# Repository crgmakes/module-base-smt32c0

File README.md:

# Servo Module

All the source files for the module template for SMT32C0-based module hardware.

# Software 

You will need [KiCad](https://kicad.org) to view and edit this design. Click [here](https://www.kicad.org/download/) to download.

You will also need all the associated libraries and models to drive the design if you want to make changes or view the 3D rendering:

https://github.com/crgmakes/kicad-library.git

Kicad MUST be configured properly to use all the files in this repo. Once you have Kicad installed, under Preferences->Configure Paths..., make the following entries:

1 - KICAD_USER_DIR -> set to the root location of where you placed the above repository.
2 - KICAD_USER_LIBRARY = ${KICAD_USER_DIR}/Library
3 - KICAD_USER_MODEL_DIR = ${KICAD_USER_LIBRARY}/models
4 - KICAD_USER_TEMPLATE_DIR	= ${KICAD_USER_LIBRARY}/templates	

Kicad will operate mostly normally if these are not set properly. You will notice an issue when you view the PCB in 3D mode.

***NOTE***: after makeing a release build in git, if your rendered 3D images are missing components, ensure the path to EVERY component model is set to ${KICAD_USER_MODEL_DIR}/<model name>.

Kicad sometimes replaces the variable with an expansion and that FAILS during the build process because the expanded variable is local and does not match the build environment.

---

THE DESIGN IS PROVIDED "AS IS" AND THE AUTHOR DISCLAIMS ALL WARRANTIES WITH REGARD TO THIS DESIGN INCLUDING ALL IMPLIED WARRANTIES OF MERCHANTABILITY AND FITNESS. IN NO EVENT SHALL THE AUTHOR BE LIABLE FOR ANY SPECIAL, DIRECT, INDIRECT, OR CONSEQUENTIAL DAMAGES OR ANY DAMAGES WHATSOEVER RESULTING FROM LOSS OF USE, DATA OR PROFITS, WHETHER IN AN ACTION OF CONTRACT, NEGLIGENCE OR OTHER TORTIOUS ACTION, ARISING OUT OF OR IN CONNECTION WITH THE USE OR PERFORMANCE OF THIS DESIGN.

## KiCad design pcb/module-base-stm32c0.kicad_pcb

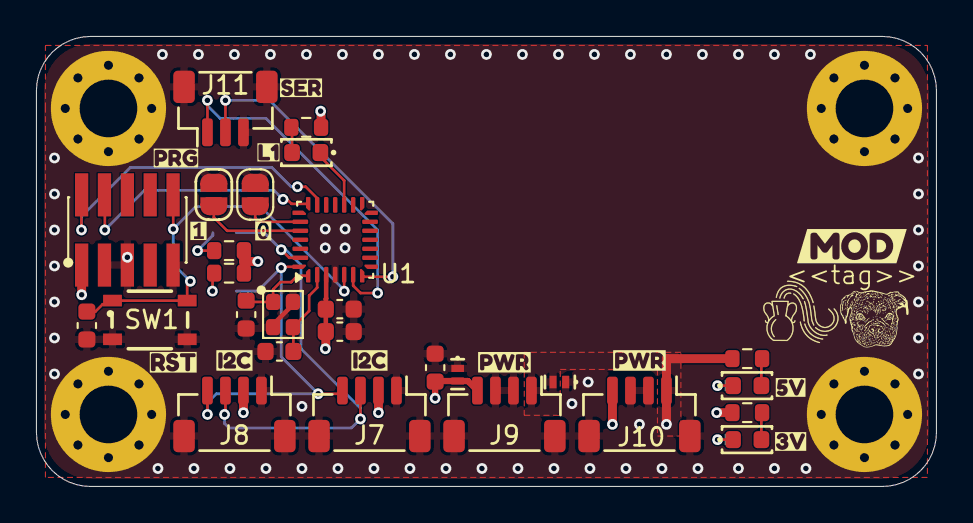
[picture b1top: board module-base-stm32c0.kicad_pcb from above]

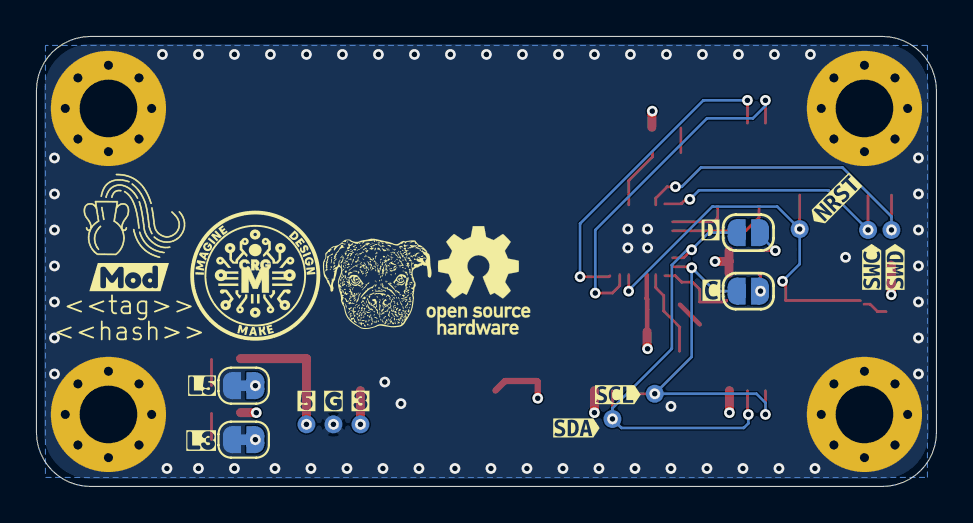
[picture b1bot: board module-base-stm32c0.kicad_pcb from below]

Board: 4 copper layers, 50.0 x 25.0 mm, 75 parts (29 on the bottom side), 22 nets.

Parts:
C1, C2: 4.7pF; C_0603_1608Metric
C3: 4.7uF; C_0603_1608Metric
C4, C5: 0.1uF; C_0603_1608Metric
C8: 10uF; C_0603_1608Metric
D1, D12, D13: Blue; LED_0603_1608Metric
D10: PESD5V5C1BL; DFN1006-2
D11: PESD3V3S1BL; DFN1006-2
H1, H2, H3, H4: MountingHole; MountingHole_3.2mm_M3_Pad_Via
J1: SWD Header; PinHeader_2x05_P1.27mm_Vertical_SMD
J7, J8, J9, J10: JST_SH_BM04B-SRSS-TB_1x04-1MP_P1.00mm_Vertical
J11: JST_SH_BM03B-SRSS-TB_1x03-1MP_P1.00mm_Vertical
JP1, JP2, JP3, JP4: SolderJumper-2_P1.3mm_Open_RoundedPad1.0x1.5mm
JP6, JP7: SolderJumper-2_P1.3mm_Bridged_RoundedPad1.0x1.5mm
LOGO1: Aquarius Logo 5mm
LOGO2: Aquarius Logo 3.5mm
LOGO3: CRGM Logo 7mm
LOGO4: Logo_Open_Hardware_Small; OSHW-Logo_5.7x6mm_SilkScreen
LOGO5: Roxy 3.5mm
LOGO6: Roxy 6.5mm
R1, R2, R8: 4.7K; R_0603_1608Metric
R3: 1K; R_0603_1608Metric
R7: 10K; R_0603_1608Metric
SW1: SKRPABE010; SMD-4P-4.2x3.2mm
TP8, TP9, TP10, TP15, TP16, TP17, TP18, TP19: TestPoint_Pad_D1.0mm
U1: STM32C031G6Ux; QFN-28_4x4mm_P0.5mm
Y1: ECS-480-10-37B2-RWN-TR; Crystal_SMD_2016-4Pin_2.0x1.6mm
kibuzzard-6A2A39A9: G***; kibuzzard-6A2A39A9
kibuzzard-6A2A39B0: G***; kibuzzard-6A2A39B0
kibuzzard-6A2B43CF: G***; kibuzzard-6A2B43CF
kibuzzard-6A2CABB7: G***; kibuzzard-6A2CABB7
kibuzzard-6A2CBD99: G***; kibuzzard-6A2CBD99
kibuzzard-6A51A315: G***; kibuzzard-6A51A315
kibuzzard-6A51A320: G***; kibuzzard-6A51A320
kibuzzard-6A51A532: G***; kibuzzard-6A51A532
kibuzzard-6A51AAF7: G***; kibuzzard-6A51AAF7
kibuzzard-6A51AB05: G***; kibuzzard-6A51AB05
kibuzzard-6A51AB65: G***; kibuzzard-6A51AB65
kibuzzard-6A51AB70: G***; kibuzzard-6A51AB70
kibuzzard-6A5157F8: G***; kibuzzard-6A5157F8
kibuzzard-6A518195: G***; kibuzzard-6A518195
kibuzzard-69C094E5: G***; kibuzzard-69C094E5
kibuzzard-69C094ED: G***; kibuzzard-69C094ED
kibuzzard-690AC3C6: G***; kibuzzard-690AC3C6
kibuzzard-690AC3CC: G***; kibuzzard-690AC3CC
kibuzzard-690AC3D2: G***; kibuzzard-690AC3D2
kibuzzard-690D5FD9: G***; kibuzzard-690D5FD9
kibuzzard-690D5FF2: G***; kibuzzard-690D5FF2
kibuzzard-6954A310: G***; kibuzzard-6954A310
kibuzzard-6954A315: G***; kibuzzard-6954A315
kibuzzard-6917603D: G***; kibuzzard-6917603D
kibuzzard-69176003: G***; kibuzzard-69176003
kibuzzard-69176035: G***; kibuzzard-69176035

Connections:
+3.3V: C3.1, C4.1, C8.1, D11.2 (K2), J1.1 (VTref), J7.2, J8.2, J9.4 (V3), J10.4 (V3), R1.2, R2.2, R3.1, R8.1, TP18.1 (1_1), U1.3 (VDD)
+5V: D10.2 (K2), J9.1 (V5), J10.1 (V5), R7.1, TP17.1 (1_1)
/MCU/A0: JP3.2 (B), U1.23 (PB3)
/MCU/A1: JP4.2 (B), U1.24 (PB4)
/MCU/STATUS: D1.1 (K), U1.17 (PC6)
/MCU/SWCLK: J1.4 (SWDCLK/TCK), TP9.1 (1_1), U1.21 (PA14-BOOT0)
/MCU/SWDIO: J1.2 (SWDIO/TMS), TP10.1 (1_1), U1.20 (PA13)
/Power/V3.3LED: D13.2 (A), R8.2
/Power/V5LED: D12.2 (A), R7.2
GND: C1.1, C2.1, C3.2, C4.2, C5.2, C8.2, D10.1 (K1), D11.1 (K1), H1.1 (1_1), H2.1 (1_1), H3.1 (1_1), H4.1 (1_1), J1.3 (GND), J1.5 (GND), J1.9 (GNDDetect), J7.0 (MP), J7.1, J7.5 (MP), J8.0 (MP), J8.1, J8.5 (MP), J9.0 (MP), J9.2 (GND), J9.3 (GND), J9.5 (MP), J10.0 (MP), J10.2 (GND), J10.3 (GND), J10.5 (MP), J11.0 (MP), J11.3, J11.4 (MP), JP3.1 (A), JP4.1 (A), JP6.1 (A), JP7.1 (A), SW1.3, SW1.4, TP19.1 (1_1), U1.4 (VSS), Y1.2 (G), Y1.4 (G)
NRST: C5.1, J1.10 (~RESET), SW1.1, SW1.2, TP8.1 (1_1), U1.5 (PF2-NRST)
unnamed: D1.2 (A), R3.2
unnamed: D12.1 (K), JP6.2 (B)
unnamed: D13.1 (K), JP7.2 (B)
unnamed: JP1.2 (B), R1.1
unnamed: JP2.2 (B), R2.1
unnamed: C2.2, U1.1 (PC14/OSCXIN), Y1.1
unnamed: C1.2, U1.2 (PC15/OSCXO), Y1.3
RXD: J11.2, U1.7 (PA1)
SCL: J7.4, J8.4, JP1.1 (A), TP15.1 (1_1), U1.28 (PB8)
SDA: J7.3, J8.3, JP2.1 (A), TP16.1 (1_1), U1.27 (PB7)
TXD: J11.1, U1.6 (PA0)

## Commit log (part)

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2026-06-13 initial checkin
